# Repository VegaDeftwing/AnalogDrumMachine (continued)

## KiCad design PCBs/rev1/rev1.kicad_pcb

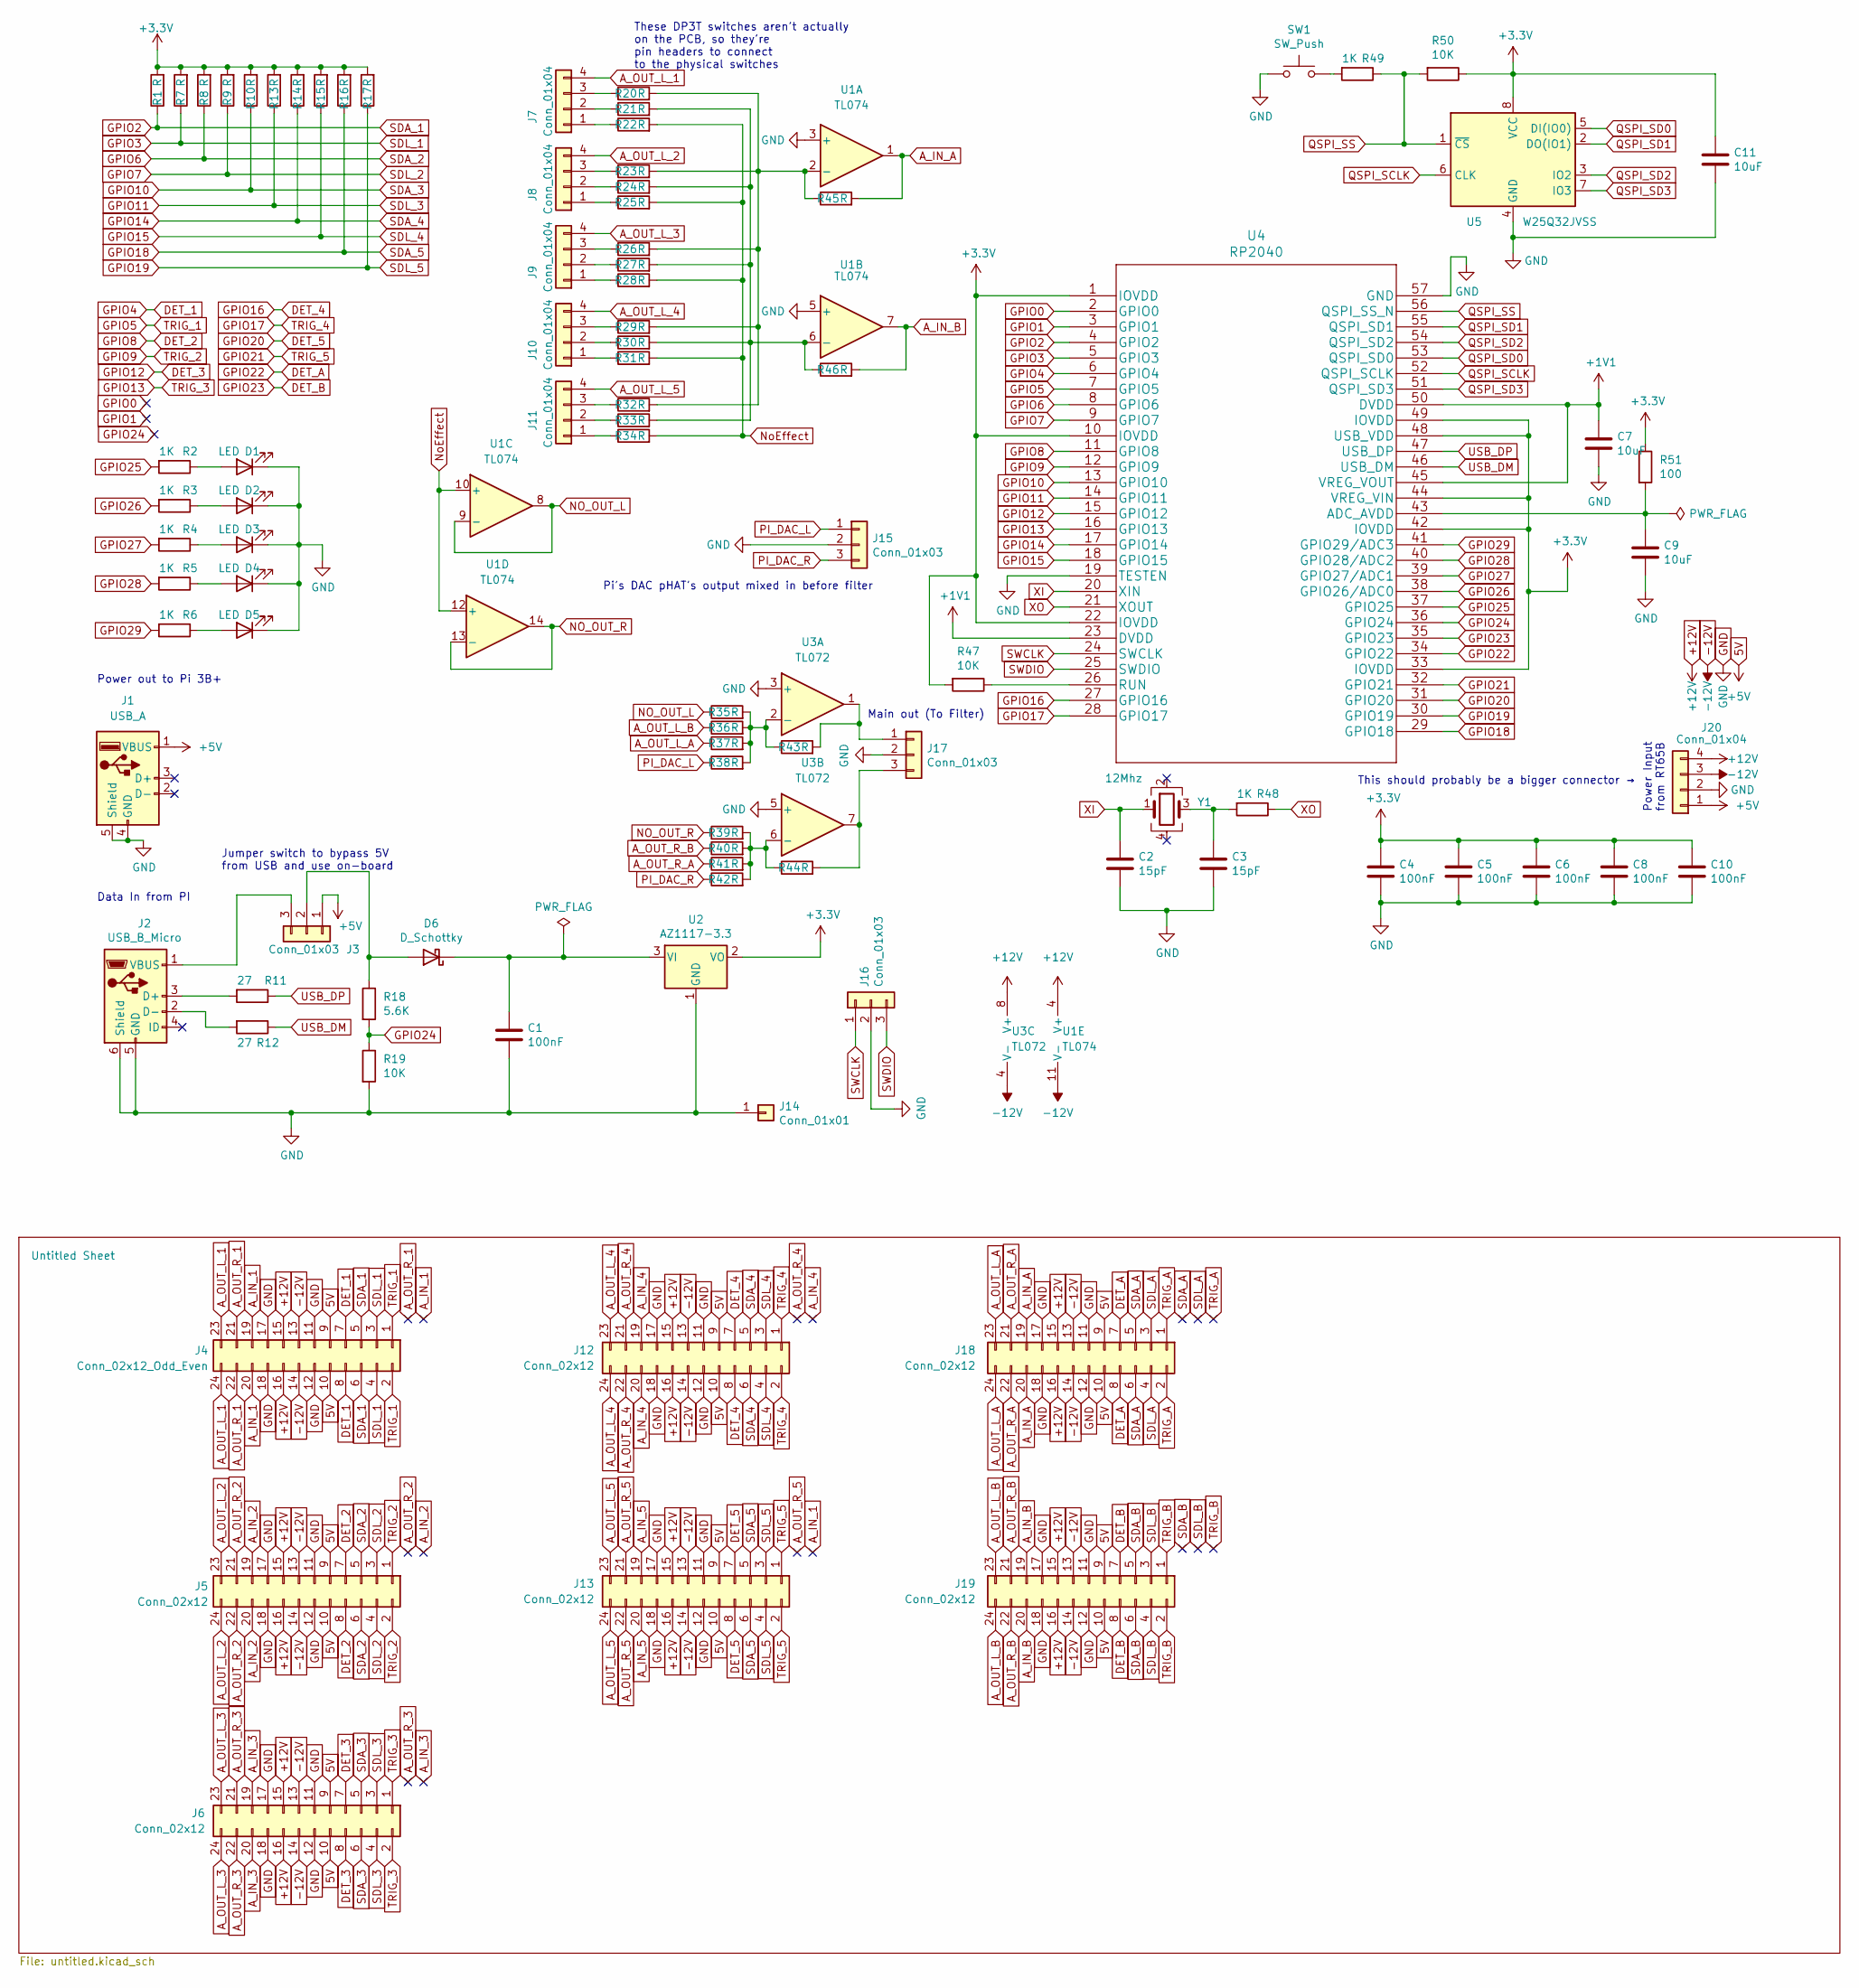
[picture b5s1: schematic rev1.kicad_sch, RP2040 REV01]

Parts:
C1, C4, C5, C6, C8, C10: 100nF; C_0805_2012Metric
C2, C3: 15pF; C_0805_2012Metric
C7, C9, C11: 10uF; C_0805_2012Metric
D1, D2, D3, D4, D5: LED; LED_0805_2012Metric
D6: D_Schottky; D_1206_3216Metric
J1: USB_A; PinHeader_1x04_P2.54mm_Vertical
J2: USB_B_Micro; USB_Micro-B_Molex_47346-0001
J3, J15, J16, J17: Conn_01x03; PinHeader_1x03_P2.54mm_Vertical
J4: Conn_02x12_Odd_Even; PinHeader_2x12_P2.54mm_Vertical
J5, J6, J12, J13, J18, J19: Conn_02x12; PinHeader_2x12_P2.54mm_Vertical
J7, J8, J9, J10, J11: Conn_01x04; PinHeader_1x04_P2.54mm_Vertical
J14: Conn_01x01; PinHeader_1x01_P2.54mm_Vertical
J20: Conn_01x04; PhoenixContact_GMSTBA_2,5_4-G_1x04_P7.50mm_Horizontal
R1, R7, R8, R9, R10, R13, R14, R15, R16, R17, R20, R21, R22, R23, R24, R25, R26, R27, R28, R29, R30, R31, R32, R33, R34, R35, R36, R37, R38, R39, R40, R41, R42, R43, R44, R45, R46: R; R_0805_2012Metric
R2, R3, R4, R5, R6, R48, R49: 1K; R_0805_2012Metric
R11, R12: 27; R_0805_2012Metric
R18: 5.6K; R_0805_2012Metric
R19, R47, R50: 10K; R_0805_2012Metric
R51: 100; R_0805_2012Metric
SW1: SW_Push; SW_SPST_CK_RS282G05A3
U1: TL074; SO-14_5.3x10.2mm_P1.27mm
U2: AZ1117-3.3; SOT-223-3_TabPin2
U3: TL072; SO-8_5.3x6.2mm_P1.27mm
U4: RP2040
U5: W25Q32JVSS; SOIC-8_5.23x5.23mm_P1.27mm
Y1: 12Mhz; Crystal_SMD_SeikoEpson_FA238-4Pin_3.2x2.5mm

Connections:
5V: J1.1 (VBUS), J3.1, J4.9, J4.10, J5.9, J5.10, J6.9, J6.10, J12.9, J12.10, J13.9, J13.10, J18.9, J18.10, J19.9, J19.10, J20.1
+1V1: C7.1, U4.23 (DVDD), U4.45 (VREG_VOUT), U4.50 (DVDD)
+3V3: C4.1, C5.1, C6.1, C8.1, C10.1, C11.1, R1.2, R7.2, R8.2, R9.2, R10.2, R13.2, R14.2, R15.2, R16.2, R17.2, R47.2, R50.1, R51.1, U2.2 (VO), U4.1 (IOVDD), U4.10 (IOVDD), U4.22 (IOVDD), U4.33 (IOVDD), U4.42 (IOVDD), U4.44 (VREG_VIN), U4.48 (USB_VDD), U4.49 (IOVDD), U5.8 (VCC)
+12V: J4.15, J4.16, J5.15, J5.16, J6.15, J6.16, J12.15, J12.16, J13.15, J13.16, J18.15, J18.16, J19.15, J19.16, J20.4, U1.4 (V+), U3.8 (V+)
-12V: J4.13, J4.14, J5.13, J5.14, J6.13, J6.14, J12.13, J12.14, J13.13, J13.14, J18.13, J18.14, J19.13, J19.14, J20.3, U1.11 (V-), U3.4 (V-)
A_IN_1: J4.19, J4.20
A_IN_2: J5.19, J5.20
A_IN_3: J6.19, J6.20
A_IN_4: J12.19, J12.20
A_IN_5: J13.19, J13.20
A_IN_A: J18.19, J18.20, R45.2, U1.1
A_IN_B: J19.19, J19.20, R46.2, U1.7
A_OUT_L_1: J4.23, J4.24, J7.4
A_OUT_L_2: J5.23, J5.24, J8.4
A_OUT_L_3: J6.23, J6.24, J9.4
A_OUT_L_4: J10.4, J12.23, J12.24
A_OUT_L_5: J11.4, J13.23, J13.24
A_OUT_L_A: J18.23, J18.24, R37.1
A_OUT_L_B: J19.23, J19.24, R36.1
A_OUT_R_1: J4.21, J4.22
A_OUT_R_2: J5.21, J5.22
A_OUT_R_3: J6.21, J6.22
A_OUT_R_4: J12.21, J12.22
A_OUT_R_5: J13.21, J13.22
A_OUT_R_A: J18.21, J18.22, R41.1
A_OUT_R_B: J19.21, J19.22, R40.1
DET_1: J4.7, J4.8, U4.6 (GPIO4)
DET_2: J5.7, J5.8, U4.11 (GPIO8)
DET_3: J6.7, J6.8, U4.15 (GPIO12)
DET_4: J12.7, J12.8, U4.27 (GPIO16)
DET_5: J13.7, J13.8, U4.31 (GPIO20)
DET_A: J18.7, J18.8, U4.34 (GPIO22)
DET_B: J19.7, J19.8, U4.35 (GPIO23)
GND: C1.2, C2.2, C3.2, C4.2, C5.2, C6.2, C7.2, C8.2, C9.2, C10.2, C11.2, D1.1 (K), D2.1 (K), D3.1 (K), D4.1 (K), D5.1 (K), J1.4 (GND), J1.5 (Shield), J2.5 (GND), J2.6 (Shield), J4.11, J4.12, J4.17, J4.18, J5.11, J5.12, J5.17, J5.18, J6.11, J6.12, J6.17, J6.18, J12.11, J12.12, J12.17, J12.18, J13.11, J13.12, J13.17, J13.18, J14.1, J15.2, J16.2, J17.2, J18.11, J18.12, J18.17, J18.18, J19.11, J19.12, J19.17, J19.18, J20.2, R19.2, SW1.1, U1.3 (+), U1.5 (+), U2.1 (GND), U3.3 (+), U3.5 (+), U4.19 (TESTEN), U4.57 (GND), U5.4 (GND)
GPIO0: U4.2 (GPIO0)
GPIO1: U4.3 (GPIO1)
GPIO2: J4.5, J4.6, R1.1, U4.4 (GPIO2)
GPIO3: J4.3, J4.4, R7.1, U4.5 (GPIO3)
GPIO5: J4.1, J4.2, U4.7 (GPIO5)
GPIO6: J5.5, J5.6, R8.1, U4.8 (GPIO6)
GPIO7: J5.3, J5.4, R9.1, U4.9 (GPIO7)
GPIO9: J5.1, J5.2, U4.12 (GPIO9)
GPIO10: J6.5, J6.6, R10.1, U4.13 (GPIO10)
GPIO11: J6.3, J6.4, R13.1, U4.14 (GPIO11)
GPIO13: J6.1, J6.2, U4.16 (GPIO13)
GPIO14: J12.5, J12.6, R14.1, U4.17 (GPIO14)
GPIO15: J12.3, J12.4, R15.1, U4.18 (GPIO15)
GPIO17: J12.1, J12.2, U4.28 (GPIO17)
GPIO18: J13.5, J13.6, R16.1, U4.29 (GPIO18)
GPIO19: J13.3, J13.4, R17.1, U4.30 (GPIO19)
GPIO21: J13.1, J13.2, U4.32 (GPIO21)
GPIO24: R18.2, R19.1, U4.36 (GPIO24)
GPIO25: R2.2, U4.37 (GPIO25)
GPIO26: R3.2, U4.38 (GPIO26/ADC0)
GPIO27: R4.2, U4.39 (GPIO27/ADC1)
GPIO28: R5.2, U4.40 (GPIO28/ADC2)
GPIO29: R6.2, U4.41 (GPIO29/ADC3)
NO_OUT_L: R35.1, U1.8, U1.9 (-)
NO_OUT_R: R39.1, U1.13 (-), U1.14
unnamed: C1.1, D6.1 (K), U2.3 (VI)
unnamed: C3.1, R48.2, Y1.3
unnamed: C9.1, R51.2, U4.43 (ADC_AVDD)
unnamed: D1.2 (A), R2.1
unnamed: D2.2 (A), R3.1
unnamed: D3.2 (A), R4.1
unnamed: D4.2 (A), R5.1
unnamed: D5.2 (A), R6.1
unnamed: D6.2 (A), J3.2, R18.1
unnamed: J2.1 (VBUS), J3.3
unnamed: J2.2 (D-), R12.2
unnamed: J2.3 (D+), R11.2
unnamed: J7.1, R22.1
unnamed: J7.2, R21.1
unnamed: J7.3, R20.1
unnamed: J8.1, R25.1
unnamed: J8.2, R24.1
unnamed: J8.3, R23.1
unnamed: J9.1, R28.1
unnamed: J9.2, R27.1
unnamed: J9.3, R26.1
unnamed: J10.1, R31.1
unnamed: J10.2, R30.1
unnamed: J10.3, R29.1
unnamed: J11.1, R34.1
unnamed: J11.2, R33.1
unnamed: J11.3, R32.1
unnamed: J17.1, R43.2, U3.1
unnamed: J17.3, R44.2, U3.7
unnamed: R20.2, R23.2, R26.2, R29.2, R32.2, R45.1, U1.2 (-)
unnamed: R21.2, R24.2, R27.2, R30.2, R33.2, R46.1, U1.6 (-)
unnamed: R35.2, R36.2, R37.2, R38.2, R43.1, U3.2 (-)
unnamed: R39.2, R40.2, R41.2, R42.2, R44.1, U3.6 (-)
unnamed: R47.1, U4.26 (RUN)
unnamed: R49.2, SW1.2
NoEffect: R22.2, R25.2, R28.2, R31.2, R34.2, U1.10 (+), U1.12 (+)
PI_DAC_L: J15.1, R38.1
PI_DAC_R: J15.3, R42.1
QSPI_SCLK: U4.52 (QSPI_SCLK), U5.6 (CLK)
QSPI_SD0: U4.53 (QSPI_SD0), U5.5 (DI(IO0))
QSPI_SD1: U4.55 (QSPI_SD1), U5.2 (DO(IO1))
QSPI_SD2: U4.54 (QSPI_SD2), U5.3 (IO2)
QSPI_SD3: U4.51 (QSPI_SD3), U5.7 (IO3)
QSPI_SS: R49.1, R50.2, U4.56 (QSPI_SS_N), U5.1 (~CS)
SDA_A: J18.5, J18.6
SDA_B: J19.5, J19.6
SDL_A: J18.3, J18.4
SDL_B: J19.3, J19.4
SWCLK: J16.1, U4.24 (SWCLK)
SWDIO: J16.3, U4.25 (SWDIO)
TRIG_A: J18.1, J18.2
TRIG_B: J19.1, J19.2
USB_DM: R12.1, U4.46 (USB_DM)
USB_DP: R11.1, U4.47 (USB_DP)
XI: C2.1, U4.20 (XIN), Y1.1
XO: R48.1, U4.21 (XOUT)

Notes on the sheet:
These DP3T switches aren't actually on the PCB, so they're pin headers to connect to the physical switches
Data In from PI
This should probably be a bigger connector →
Power Input from RT65B
Pi's DAC pHAT's output mixed in before filter
Main out (To Filter)
Power out to Pi 3B+
Jumper switch to bypass 5V from USB and use on-board

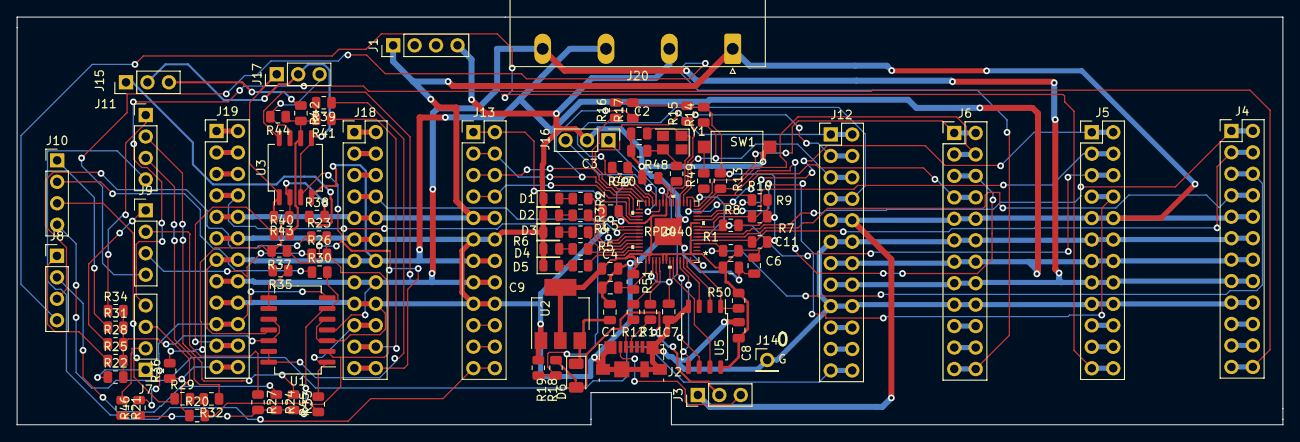
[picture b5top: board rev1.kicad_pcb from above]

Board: 2 copper layers, 149.9 x 48.3 mm, 95 parts (0 on the bottom side), 113 nets.

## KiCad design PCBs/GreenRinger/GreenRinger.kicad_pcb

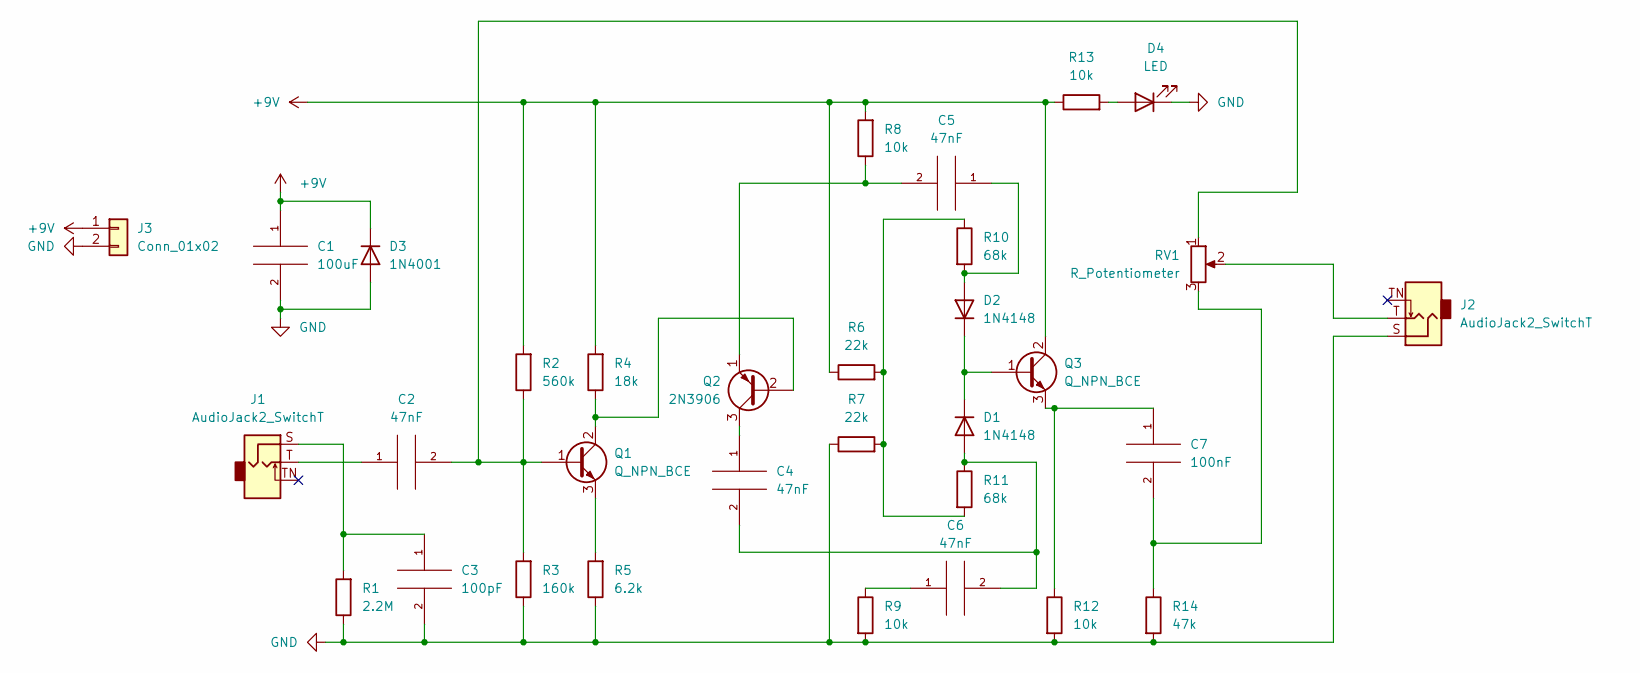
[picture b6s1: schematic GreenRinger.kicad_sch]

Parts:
C1: 100uF; CP_Radial_D4.0mm_P1.50mm
C2, C4, C5, C6: 47nF; C_Disc_D3.8mm_W2.6mm_P2.50mm
C3: 100pF; C_Disc_D3.8mm_W2.6mm_P2.50mm
C7: 100nF; C_Disc_D3.8mm_W2.6mm_P2.50mm
D1, D2: 1N4148; D_DO-35_SOD27_P7.62mm_Horizontal
D3: 1N4001; D_DO-41_SOD81_P10.16mm_Horizontal
D4: LED; LED_D1.8mm_W3.3mm_H2.4mm
J1, J2: AudioJack2_SwitchT; Jack_3.5mm_QingPu_WQP-PJ398SM_Vertical_CircularHoles
J3: Conn_01x02; PinHeader_1x02_P1.00mm_Vertical
Q1, Q3: Q_NPN_BCE; TO-92_Inline
Q2: 2N3906; TO-92_Inline
R1: 2.2M; R_Axial_DIN0204_L3.6mm_D1.6mm_P5.08mm_Horizontal
R2: 560k; R_Axial_DIN0204_L3.6mm_D1.6mm_P5.08mm_Horizontal
R3: 160k; R_Axial_DIN0204_L3.6mm_D1.6mm_P5.08mm_Horizontal
R4: 18k; R_Axial_DIN0204_L3.6mm_D1.6mm_P5.08mm_Horizontal
R5: 6.2k; R_Axial_DIN0204_L3.6mm_D1.6mm_P5.08mm_Horizontal
R6, R7: 22k; R_Axial_DIN0204_L3.6mm_D1.6mm_P5.08mm_Horizontal
R8, R9, R12, R13: 10k; R_Axial_DIN0204_L3.6mm_D1.6mm_P5.08mm_Horizontal
R10, R11: 68k; R_Axial_DIN0204_L3.6mm_D1.6mm_P5.08mm_Horizontal
R14: 47k; R_Axial_DIN0204_L3.6mm_D1.6mm_P5.08mm_Horizontal
RV1: R_Potentiometer; Potentiometer_ACP_CA9-V10_Vertical

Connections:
+9V: C1.1, D3.1 (K), J3.1, Q3.2 (C), R2.2, R4.2, R6.1, R8.2, R13.1
GND: C1.2, C3.2, D3.2 (A), D4.1 (K), J2.S, J3.2, R1.1, R3.1, R5.1, R7.1, R9.2, R12.2, R14.2
unnamed: C2.1, J1.T
unnamed: C3.1, J1.S, R1.2
unnamed: C6.1, R9.1
unnamed: C7.2, R14.1, RV1.3
unnamed: C4.2, C6.2, D1.2 (A), R11.1
unnamed: C5.1, D2.2 (A), R10.2
unnamed: D4.2 (A), R13.2
unnamed: J2.T, RV1.2
unnamed: C2.2, Q1.1 (B), R2.1, R3.2, RV1.1
unnamed: Q1.2 (C), Q2.2 (B), R4.1
unnamed: Q1.3 (E), R5.2
unnamed: C5.2, Q2.1 (E), R8.1
unnamed: C4.1, Q2.3 (C)
unnamed: D1.1 (K), D2.1 (K), Q3.1 (B)
unnamed: C7.1, Q3.3 (E), R12.1
unnamed: R6.2, R7.2, R10.1, R11.2

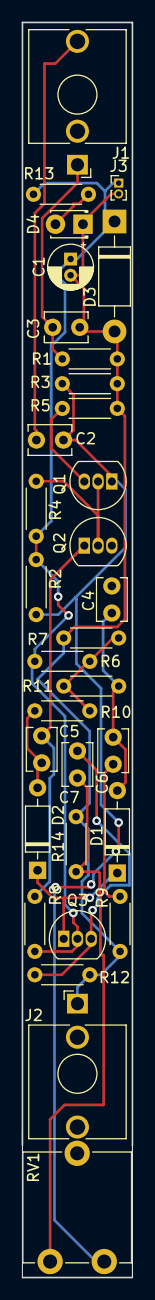
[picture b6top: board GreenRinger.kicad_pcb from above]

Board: 2 copper layers, 10.2 x 116.0 mm, 32 parts (0 on the bottom side), 18 nets.

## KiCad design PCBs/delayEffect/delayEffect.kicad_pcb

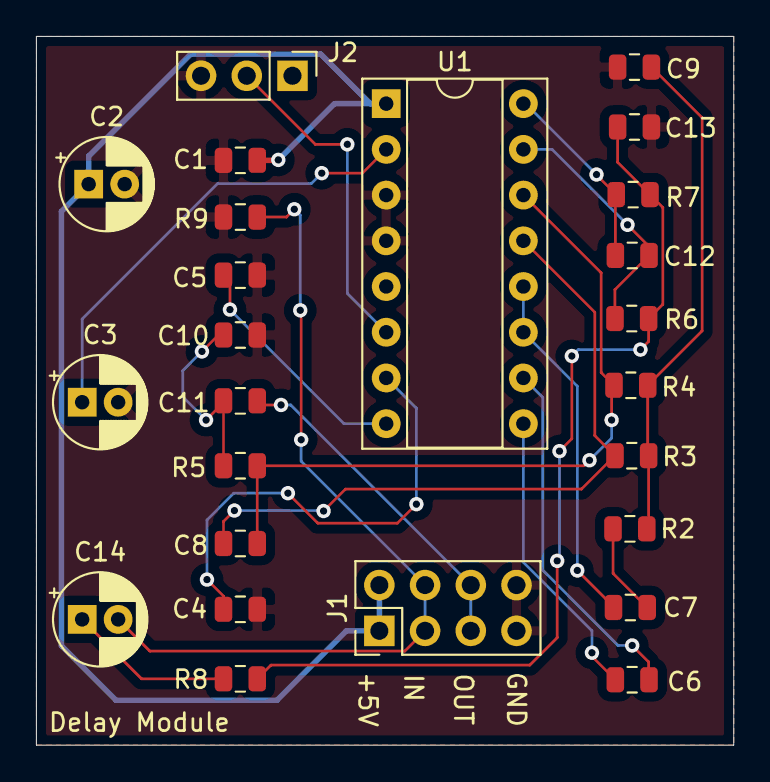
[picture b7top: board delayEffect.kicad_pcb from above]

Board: 2 copper layers, 38.7 x 39.4 mm, 25 parts (0 on the bottom side), 20 nets.

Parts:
C1, C4, C5, C6, C7: .1uF; C_0805_2012Metric
C2: 100uF; CP_Radial_D5.0mm_P2.00mm
C3: 47uF; CP_Radial_D5.0mm_P2.00mm
C8, C12: 560pF; C_0805_2012Metric
C9, C13: 5600pF; C_0805_2012Metric
C10: .01uF; C_0805_2012Metric
C11: 10uF; C_0805_2012Metric
C14: 4.7uF; CP_Radial_D5.0mm_P2.00mm
J1: Conn_02x04_Odd_Even; PinHeader_2x04_P2.54mm_Vertical
J2: Conn_01x03; PinHeader_1x03_P2.54mm_Vertical
R2, R4, R6, R8: 15k; R_0805_2012Metric
R3, R7: 10k; R_0805_2012Metric
R5: 2.7k; R_0805_2012Metric
R9: 100k; R_0805_2012Metric
U1: PT2399; DIP-16_W7.62mm_Socket

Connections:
+5V: C1.1, C2.1, J1.1, J1.2, U1.1
GND: C1.2, C2.2, C3.2, C4.2, C5.2, C9.2, C10.2, C13.2, J1.7, J1.8, J2.3, R9.1, U1.3, U1.4
Input: C14.2, J1.3, J1.4, R9.2
unnamed: C3.1, U1.2
unnamed: C4.1, U1.7
unnamed: C5.1, U1.8
unnamed: C6.1, U1.10
unnamed: C6.2, U1.9
unnamed: C7.1, R2.2
unnamed: C7.2, U1.11, U1.12
unnamed: C8.1, R4.2, R5.2, U1.14
unnamed: C8.2, R3.2, U1.13
unnamed: C9.1, R2.1, R3.1, R4.1
unnamed: C10.1, C11.1, R5.1
unnamed: C12.1, R7.2, U1.16
unnamed: C12.2, R6.2, U1.15
unnamed: C13.1, R6.1, R7.1, R8.2
unnamed: C14.1, R8.1
unnamed: J2.2, U1.6
Output: C11.2, J1.5, J1.6

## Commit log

2021-08-25 Mock up, Basic ideas & Features
2021-08-25 quick mock up fix
2021-08-25 quick mock up fix, again
2021-08-25 quick mock up fix, the third
2021-08-25 add individual bus outs to mock up
2021-08-25 quick mock up fix, the fourth - TRS MIDI floating
2021-08-26 Added Journal, file org
2021-08-26 Journal update
2021-08-27 Meeting1
2021-08-30 Drum Selection Document
2021-08-31 added link to vactrol info
2021-08-31 Effects Selection, typo fixes
2021-09-02 Seq & Bus start, added minutes w/ Bauer
2021-09-03 Seq & Bus cont.
2021-09-03 Friday Meeting
2021-09-08 Add files via upload
    Minutes 09/08/21
2021-09-17 I'm to tired to write a good commit message
2021-09-18 journal update, minutes, and productspec2 start
2021-10-08 not sure why I never pushed all of this
2021-10-15 MinutesOct13
2021-10-19 working on classes
2021-10-20 continued work on defining classes
2021-10-25 Journal Update++
2021-10-26 Code
2021-10-29 Pattern sequencing
2021-11-08 Create Files
2021-11-08 Create PCBs
2021-11-08 Create FM
2021-11-08 Add files via upload
    FM DRUM STUFF
2021-11-13 massive code update
2021-11-13 w12 journal
2021-11-15 Create test
2021-12-08 first sounds from the sequencer... ish
2022-02-12 Lots of changes. I haven't commited or pushed in way to long
2022-02-12 making the code pretty
2022-02-14 Digipot library and example code
    Include the folder containing header and source code in Arduino ide. Sketch->Include Library->Add .zip library
2022-02-19 massive code refactor
2022-02-19 main controller PCB + many journals, images, etc.
2022-02-22 start of paramater UI code
2022-02-23 per step display code finishe
2022-03-02 microstep live editing works
2022-03-02 WIP: Change Digital Drum's play_step() for step locking
2022-03-03 fix data object not being independent per microstep
2022-03-03 base real time editing, display improvments, hiding startup time
2022-03-04 PCB
    dhwiqodhiowq
2022-03-11 RP2040 BOM
2022-03-11 BOM change
2022-03-11 Alphabetized BOM
2022-03-11 update purrdata patch, add sample display code
2022-03-11 added green ringer PCB
2022-03-15 Control Board BOM
    -noted what we currently have in stock
2022-03-25 oops, forgot to add rev5 spec
2022-03-25 fix images
2022-03-25 PROJECT SPEC 6
    Added Project Spec 6
2022-03-26 many bug fixes, pattern sequencing, copy/paste, save/restore
2022-04-01 bass drum v2, delay, and green ringer
2022-04-05 add openscad file
2022-04-05 GERBER
2022-04-08 Updated OpenSCAD
2022-04-18 delay effect
2022-04-19 control board hihat and bass
    -code.py successfully sending I2C over multiple ports, sending triggers, and flashing LEDs
2022-04-22 update journal
2022-04-22 add current keyboard code, needs to be in QMK keyboards to use
2022-04-27 updates from pi
2022-04-29 fix drum selection display
2022-05-01 Control Board Code 05/01/2022
    -test from friday
    -working hihat and snare
2022-05-01 fix minor logic issue affecting UI
2022-05-02 05/01/2022
    -successful hihat, snare and digital drum test
    -fixed GP3 bug
2022-05-05 k
    n
2022-05-05 Power Stuff
2022-05-10 DADAD
    DAADAD
2022-05-11 control board code final commit
